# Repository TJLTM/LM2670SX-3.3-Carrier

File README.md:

# LM2670SX-Carrier

A basic carrier for the LM2670SX a step down 3 amp switching regulator by TI. Selecting the correct version -3.3 -5 and the -12 for the fixed output value you need. If you need the Adjustable Model then use the -Adj project and Files. They are Drop-in / Pin Compatible but require a change in schematics to make them work for the application. 

The values I have are for a Vin == 12 Volts Vout == 3.3 and current of 3A. Please reference the data sheet for the values of L1 and the Capacitors for your Vin&&Amp requirements. If using the ADJ version you will have to reference the datasheet for the correct design and value selection for the Resistors/Cap/Inductor Values.

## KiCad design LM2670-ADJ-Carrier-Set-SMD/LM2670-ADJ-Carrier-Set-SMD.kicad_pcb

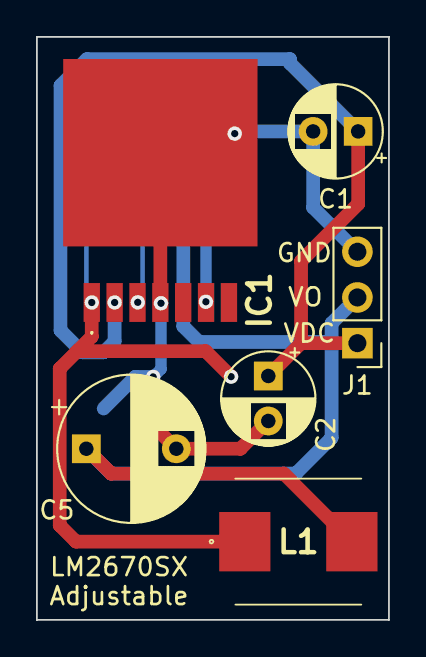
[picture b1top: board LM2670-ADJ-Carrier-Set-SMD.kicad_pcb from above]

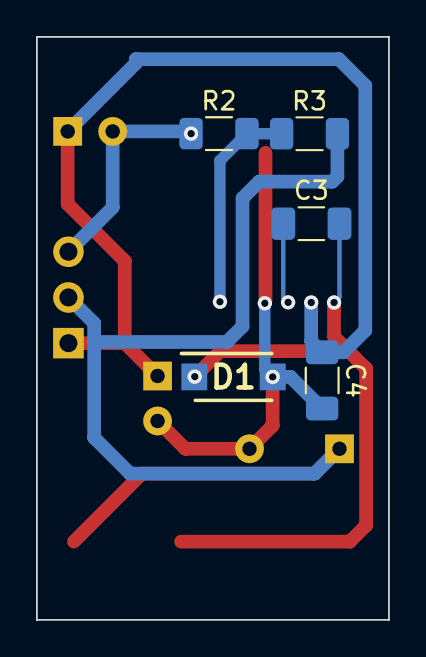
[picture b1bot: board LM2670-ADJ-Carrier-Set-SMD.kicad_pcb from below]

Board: 2 copper layers, 19.6 x 32.4 mm, 11 parts (5 on the bottom side), 6 nets.

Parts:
C1, C2: 15uF; CP_Radial_D5.0mm_P2.50mm
C3: 0.1uF; C_1206_3216Metric_Pad1.33x1.80mm_HandSolder
C4: 0.47uF; C_1206_3216Metric_Pad1.33x1.80mm_HandSolder
C5: 120uF; CP_Radial_D8.0mm_P5.00mm
D1: VSSAF3N50-M3_6A; SODFL5226X100N
IC1: LM2670SX-3.3_NOPB; LM2670SX33NOPB
J1: Conn_01x03; PinHeader_1x03_P2.54mm_Vertical
L1: SPM7054VT-330M-D; SPM7054VT
R2, R3: 4.7K; R_1206_3216Metric_Pad1.30x1.75mm_HandSolder

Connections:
+VDC: C1.1, C2.1, C4.1, IC1.2 (INPUT), J1.1
GND: C1.2, C2.2, C4.2, C5.2, D1.2, IC1.4 (GND), IC1.8 (EP), J1.3, R2.1
unnamed: C3.1, IC1.3 (CBOOST/CB)
unnamed: IC1.6 (FEEDBACK/FB), R2.2, R3.1
unnamed: C3.2, D1.1, IC1.1 (SWITCH_OUTPUT), L1.1
unnamed: C5.1, J1.2, L1.2, R3.2

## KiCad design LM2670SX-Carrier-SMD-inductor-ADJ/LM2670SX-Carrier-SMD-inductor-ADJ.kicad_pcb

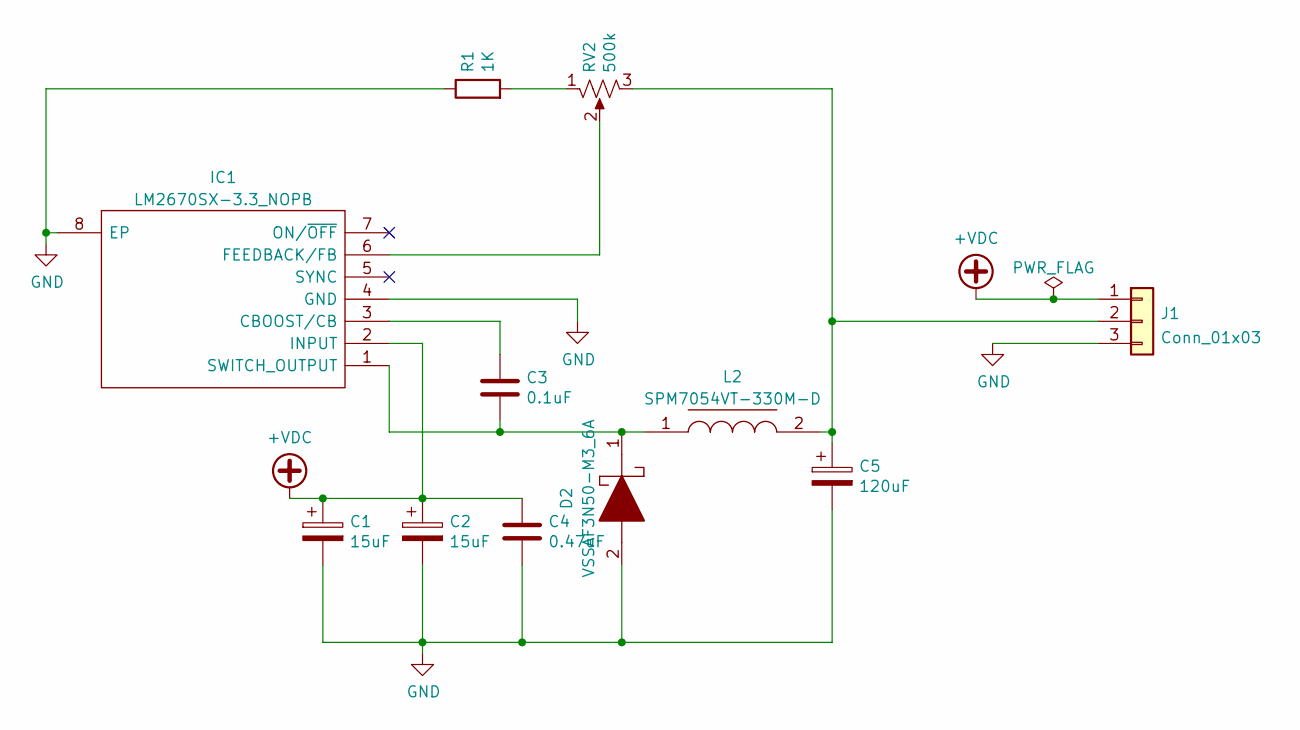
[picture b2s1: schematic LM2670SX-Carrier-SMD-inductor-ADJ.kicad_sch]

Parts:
C1, C2: 15uF; CP_Radial_D5.0mm_P2.50mm
C3: 0.1uF; C_1206_3216Metric_Pad1.33x1.80mm_HandSolder
C4: 0.47uF; C_1206_3216Metric_Pad1.33x1.80mm_HandSolder
C5: 120uF; CP_Radial_D8.0mm_P5.00mm
D2: VSSAF3N50-M3_6A; SODFL5226X100N; Mouser Part Number 78-VSSAF3N50-M36A
IC1: LM2670SX-3.3_NOPB; LM2670SX33NOPB; Mouser Part Number 926-LM2670SX33NOPB
J1: Conn_01x03; PinHeader_1x03_P2.54mm_Vertical
L2: SPM7054VT-330M-D; SPM7054VT; Mouser Part Number 810-SPM7054VT-330M-D
R1: 1K; R_1206_3216Metric_Pad1.30x1.75mm_HandSolder
RV2: 500k; Potentiometer_Bourns_3296W_Vertical

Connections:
+VDC: C1.1, C2.1, C4.1, IC1.2 (INPUT), J1.1
GND: C1.2, C2.2, C4.2, C5.2, D2.2, IC1.4 (GND), IC1.8 (EP), J1.3, R1.1
unnamed: C3.1, IC1.3 (CBOOST/CB)
unnamed: IC1.6 (FEEDBACK/FB), RV2.2
unnamed: C3.2, D2.1, IC1.1 (SWITCH_OUTPUT), L2.1
unnamed: C5.1, J1.2, L2.2, RV2.3
unnamed: R1.2, RV2.1

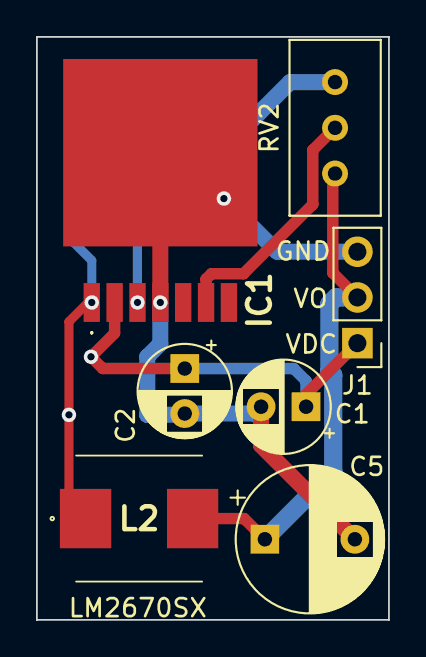
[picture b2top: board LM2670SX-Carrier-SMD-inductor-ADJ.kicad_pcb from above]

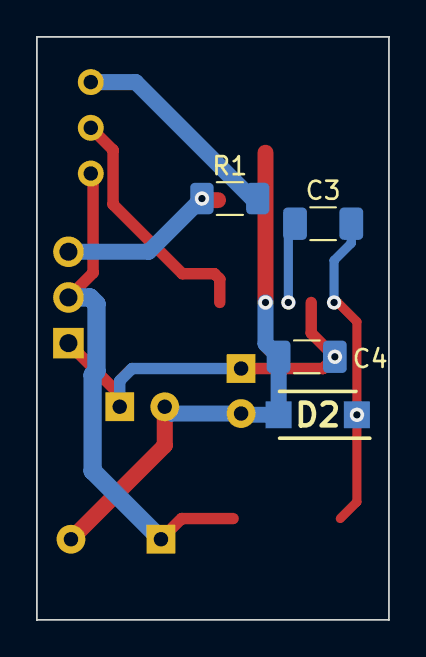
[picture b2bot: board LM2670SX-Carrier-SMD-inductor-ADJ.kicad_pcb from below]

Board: 2 copper layers, 19.6 x 32.4 mm, 11 parts (4 on the bottom side), 7 nets.

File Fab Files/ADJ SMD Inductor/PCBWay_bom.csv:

designator,quantity,value,pack,mpn,mount_type
"C1, C2",2,15uF,CP_Radial_D5.0mm_P2.50mm,,tht
C3,1,0.1uF,C_1206_3216Metric_Pad1.33x1.80mm_HandSolder,,smt
C4,1,0.47uF,C_1206_3216Metric_Pad1.33x1.80mm_HandSolder,,smt
C5,1,120uF,CP_Radial_D8.0mm_P5.00mm,,tht
D2,1,VSSAF3N50-M3_6A,SODFL5226X100N,,smt
IC1,1,LM2670SX-3.3_NOPB,LM2670SX33NOPB,,smt
J1,1,Conn_01x03,PinHeader_1x03_P2.54mm_Vertical,,tht
L2,1,SPM7054VT-330M-D,SPM7054VT,,smt
R1,1,1K,R_1206_3216Metric_Pad1.30x1.75mm_HandSolder,,smt
RV2,1,500k,Potentiometer_Bourns_3296W_Vertical,,tht

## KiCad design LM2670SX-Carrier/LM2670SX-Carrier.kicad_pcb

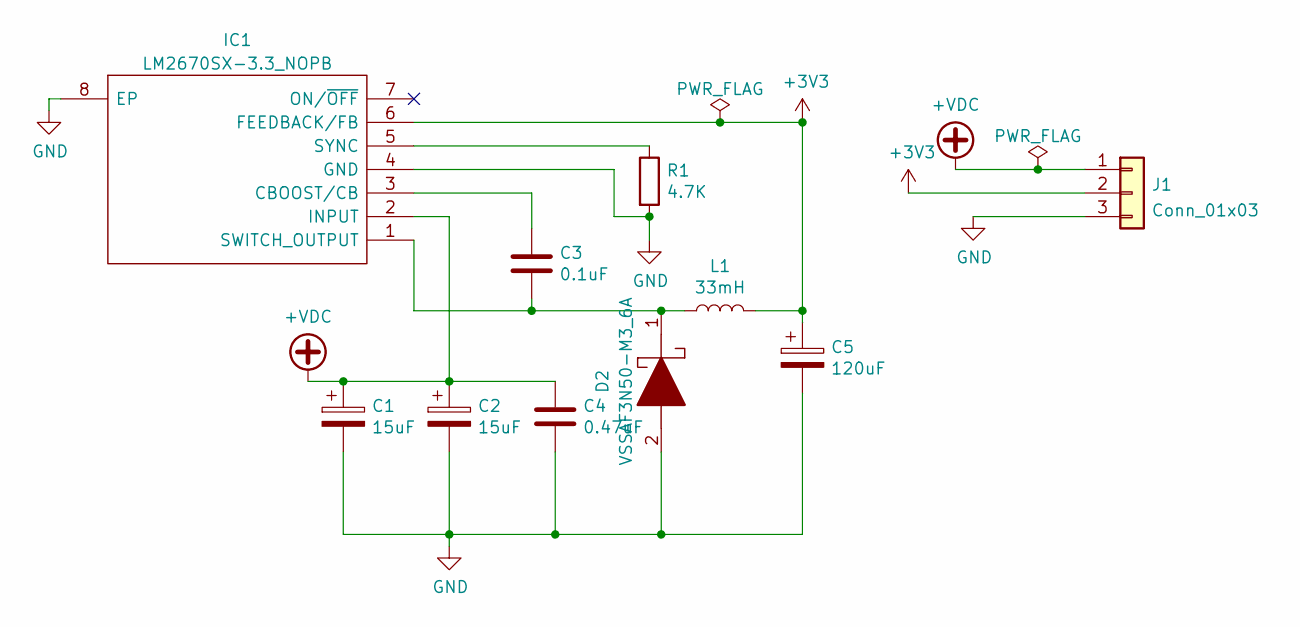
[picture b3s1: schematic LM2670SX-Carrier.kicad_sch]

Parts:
C1, C2: 15uF; CP_Radial_D5.0mm_P2.50mm
C3: 0.1uF; C_0603_1608Metric_Pad1.08x0.95mm_HandSolder
C4: 0.47uF; C_0603_1608Metric_Pad1.08x0.95mm_HandSolder
C5: 120uF; CP_Radial_D8.0mm_P5.00mm
D2: VSSAF3N50-M3_6A; SODFL5226X100N; Mouser Part Number 78-VSSAF3N50-M36A
IC1: LM2670SX-3.3_NOPB; LM2670SX33NOPB; Mouser Part Number 926-LM2670SX33NOPB
J1: Conn_01x03; PinHeader_1x03_P2.54mm_Vertical
L1: 33mH; L_Axial_L9.5mm_D4.0mm_P15.24mm_Horizontal_Fastron_SMCC
R1: 4.7K; R_0612_1632Metric_Pad1.18x3.40mm_HandSolder

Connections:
+3V3: C5.1, IC1.6 (FEEDBACK/FB), J1.2, L1.2
+VDC: C1.1, C2.1, C4.1, IC1.2 (INPUT), J1.1
GND: C1.2, C2.2, C4.2, C5.2, D2.2, IC1.4 (GND), IC1.8 (EP), J1.3, R1.2
unnamed: C3.1, IC1.3 (CBOOST/CB)
unnamed: C3.2, D2.1, IC1.1 (SWITCH_OUTPUT), L1.1
unnamed: IC1.5 (SYNC), R1.1

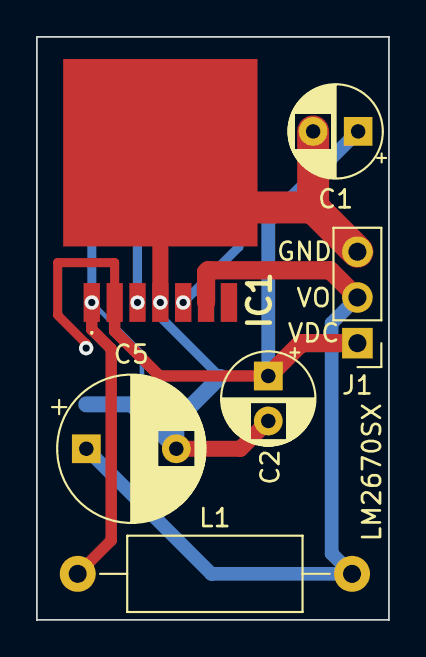
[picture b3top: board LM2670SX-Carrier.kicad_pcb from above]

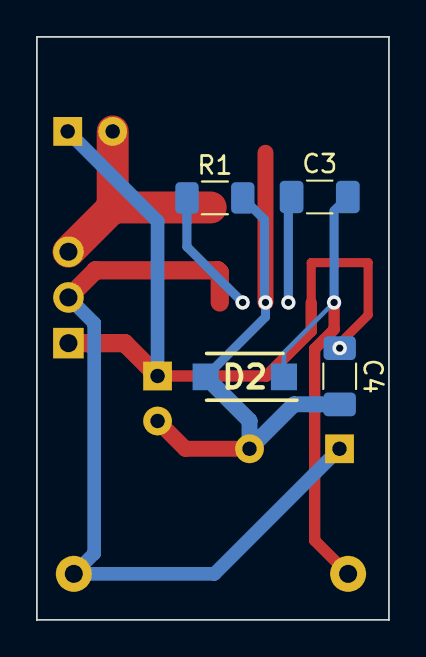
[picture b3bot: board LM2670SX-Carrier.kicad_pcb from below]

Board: 2 copper layers, 19.6 x 32.4 mm, 10 parts (4 on the bottom side), 6 nets.

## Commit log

2023-04-02 initial.
2023-04-04 finished and drc'ed
2023-04-04 adding datasheet
2023-04-04 adding fab files
2023-04-28 fixing some routes and DRC'ed it.
2023-05-04 rename
2023-05-04 adding boms
2023-05-04 removing old 3.3 and adding the "fixed" folder for the 3.3 5 12 volt models.
2023-05-08 adding an adjustable variation. Pre-selected resistor values for R2 R3 will give you your desired output voltage.
2023-05-08 finished ADJ board and adding the Fab Files for it.
2023-05-17 adding smd inductor mod board
2023-05-19 adding fab files for Fixed SMD inductror adding that as well. sent off to fab
2023-05-24 adding SMD inductor ADJ model.
2023-06-02 updating and adding some more of these. sending off to fab.
2024-10-01 clean up p1
2024-10-01 clean up p2
    removed pcb zips
    upgraded projects to kicad 8
2024-10-01 update footprints in schematic only
2024-10-01 ADJ Carrier SMD
2024-10-01 switching out the fab files
2024-10-02 update reg carrier
2024-10-02 adj smd inductor update
2024-10-07 update the BOMs
2024-10-07 Adding the SMD ADJ fab files
